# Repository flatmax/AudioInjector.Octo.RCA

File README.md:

# AudioInjector.Octo.RCA

The Audio Injector Octo sound card for the Raspberry Pi - RCA breakouts.
Find more information at : http://audioinjector.net

These KiCad (http://kicad.org/) files give both the schematic and PCB
gerber layouts for the RCA breakouts for the Audio Injector Octo sound
card.

These single ended breakout boards are derived from the manufacturer's data sheet specifications for single ended breakouts of the codec used in the Octo sound card.

Matt Flax
flatmax.com

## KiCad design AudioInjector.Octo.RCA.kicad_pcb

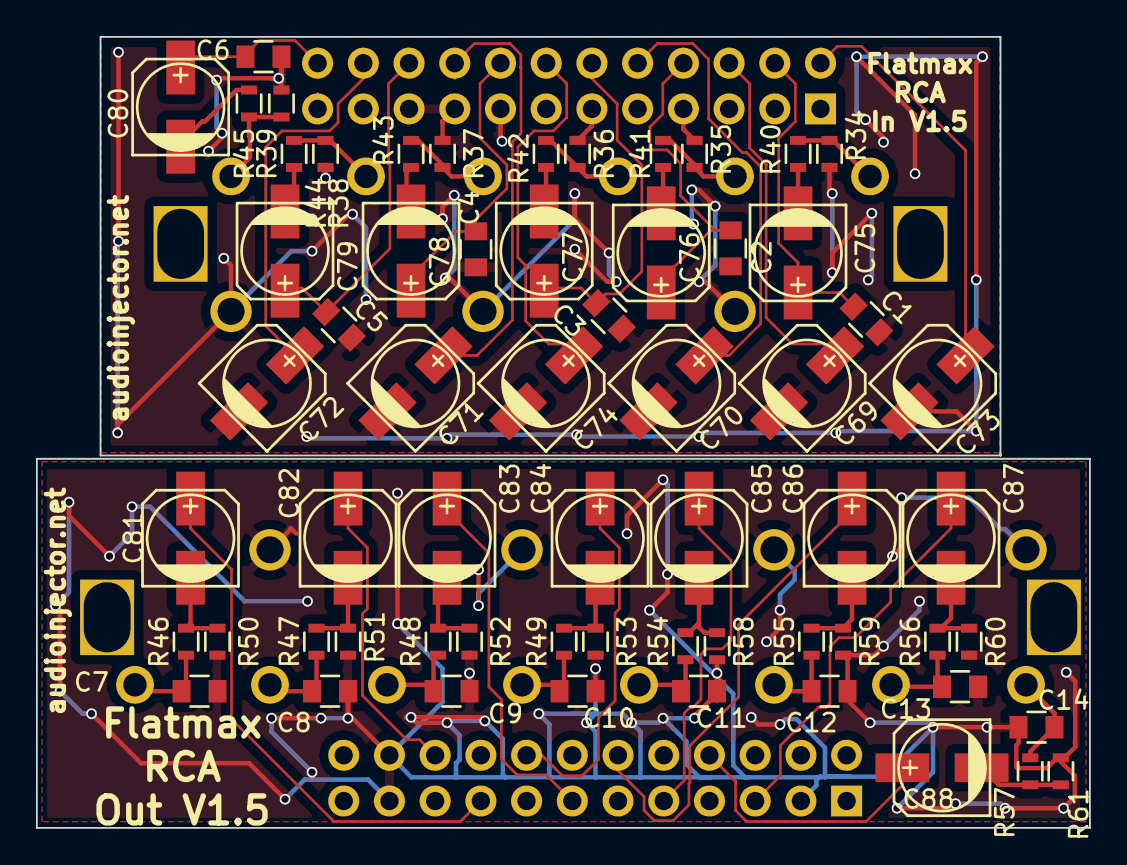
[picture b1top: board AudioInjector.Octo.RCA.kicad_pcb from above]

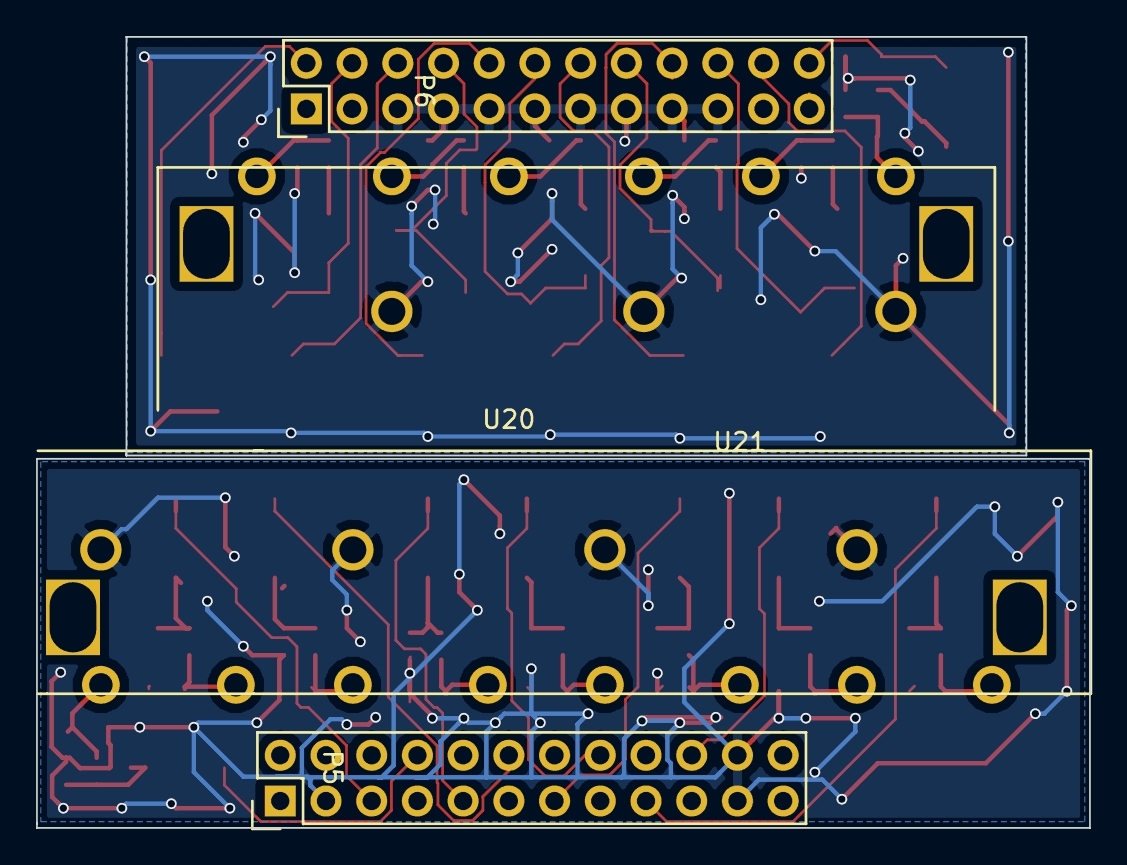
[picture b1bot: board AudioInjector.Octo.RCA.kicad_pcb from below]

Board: 2 copper layers, 58.5 x 43.9 mm, 66 parts (4 on the bottom side), 50 nets.

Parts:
C1, C2, C3, C4, C5, C6: 2.7n; C_0805
C7, C8, C9, C10, C11, C12, C13, C14: 1.5n; C_0805
C69, C70, C71, C72, C73, C74, C75, C76, C77, C78, C79, C80, C81, C82, C83, C84, C85, C86, C87, C88: 10u; c_elec_5x5.3
P5: DAC_out; Pin_Header_Straight_2x12
P6: ADC_in; Pin_Header_Straight_2x12
R34, R35, R36, R37, R38, R39: 100k; R_0603
R40, R41, R42, R43, R44, R45: 150; R_0603
R46, R47, R48, R49, R54, R55, R56, R57: 562; R_0603
R50, R51, R52, R53, R58, R59, R60, R61: 10k; R_0603
U20: AV6-8.4-13
U21: AV8-8.4-13

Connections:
/Codec/ADC_fb1+: C1.1, C75.1, P6.4
/Codec/ADC_fb1-: C73.1, P6.2
/Codec/ADC_fb2+: C2.1, C76.1, P6.8
/Codec/ADC_fb2-: C69.1, P6.6
/Codec/ADC_fb3+: C3.1, C77.1, P6.12
/Codec/ADC_fb3-: C70.1, P6.10
/Codec/ADC_fb4+: C4.1, C78.1, P6.16
/Codec/ADC_fb4-: C74.1, P6.14
/Codec/ADC_fb5+: C5.1, C79.1, P6.20
/Codec/ADC_fb5-: C71.1, P6.18
/Codec/ADC_fb6+: C6.1, C80.1, P6.24
/Codec/ADC_fb6-: C72.1, P6.22
/Codec/AGND: C1.2, C2.2, C3.2, C4.2, C5.2, C6.2, C7.2, C8.2, C9.2, C10.2, C11.2, C12.2, C13.2, C14.2, C69.2, C70.2, C71.2, C72.2, C73.2, C74.2, P5.3, P5.21, P5.22, P6.5, P6.7, P6.9, P6.11, P6.13, P6.15, P6.17, P6.19, R34.2, R35.2, R36.2, R37.2, R38.2, R39.2, R50.2, R51.2, R52.2, R53.2, R58.2, R59.2, R60.2, R61.2, U20.1, U20.4, U20.7, U21.1, U21.4, U21.7, U21.10
/Codec/AOUT1+: C81.1, P5.17
/Codec/AOUT2+: C82.1, P5.20
/Codec/AOUT3+: C83.1, P5.13
/Codec/AOUT4+: C84.1, P5.16
/Codec/AOUT5+: C85.1, P5.9
/Codec/AOUT6+: C86.1, P5.12
/Codec/AOUT7+: C87.1, P5.5
/Codec/AOUT8+: C88.1, P5.8
/Codec/In1: R34.1, R40.2, U20.2
/Codec/In2: R35.1, R41.2, U20.3
/Codec/In3: R36.1, R42.2, U20.5
/Codec/In4: R37.1, R43.2, U20.6
/Codec/In5: R38.1, R44.2, U20.8
/Codec/In6: R39.1, R45.2, U20.9
/Codec/Out1: C7.1, R46.2, U21.2
/Codec/Out2: C8.1, R47.2, U21.3
/Codec/Out3: C9.1, R48.2, U21.5
/Codec/Out4: C10.1, R49.2, U21.6
/Codec/Out5: C11.1, R54.2, U21.8
/Codec/Out6: C12.1, R55.2, U21.9
/Codec/Out7: C13.1, R56.2, U21.11
/Codec/Out8: C14.1, R57.2, U21.12
unnamed: C75.2, R40.1
unnamed: C76.2, R41.1
unnamed: C77.2, R42.1
unnamed: C78.2, R43.1
unnamed: C79.2, R44.1
unnamed: C80.2, R45.1
unnamed: C81.2, R46.1, R50.1
unnamed: C82.2, R47.1, R51.1
unnamed: C83.2, R48.1, R52.1
unnamed: C84.2, R49.1, R53.1
unnamed: C85.2, R54.1, R58.1
unnamed: C86.2, R55.1, R59.1
unnamed: C87.2, R56.1, R60.1
unnamed: C88.2, R57.1, R61.1
V5: P5.1, P5.2, P5.23, P5.24, P6.1, P6.3, P6.21, P6.23

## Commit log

2017-02-15 Initial commit of the Audio Injector Octo RCA breakout. V1.3
2017-02-15 Put a little info in the README.md
2017-02-15 More info into the readme.
2017-02-18 Fixed a bug in the output circuit. Updated part values.
2017-06-02 Adding v1.5 of these PCBs.
2017-06-15 Reversed two resistor label names.
2017-07-18 Added a pdf of the schematic.
2017-08-26 Added recorded 1kHz tones used for noise testing.
2018-11-06 Added pcb images
2021-11-08 Update README.md
    https://forum.kicad.info/t/warning-avoid-all-links-to-kicad-pcb-org-use-kicad-org/31521
